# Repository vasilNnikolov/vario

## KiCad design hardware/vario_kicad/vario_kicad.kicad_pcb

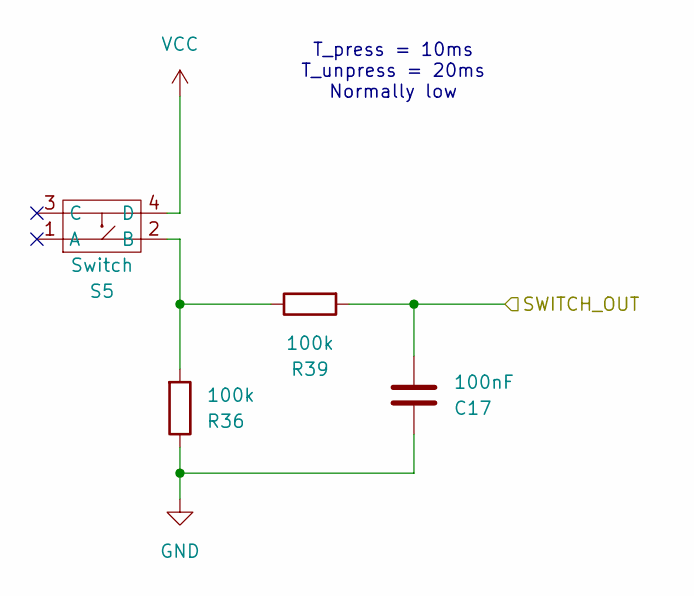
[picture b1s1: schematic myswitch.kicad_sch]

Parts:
C17: 100nF; C_0402_1005Metric
R36, R39: 100k; R_0402_1005Metric
S5: Switch; TS-1187A-B-A-B_switch

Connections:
/mcu/WKUP1: C17.2, R39.2; also elsewhere on the board
GND: C17.1, R36.1; also elsewhere on the board
unnamed: R36.2, R39.1, S5.2 (B)
VCC: S5.4 (D); also elsewhere on the board

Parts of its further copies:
C16, C28: 100nF; C_0402_1005Metric
R27, R37, R38, R40: 100k; R_0402_1005Metric
S4, S6: Switch; TS-1187A-B-A-B_switch

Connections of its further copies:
/mcu/SW1: C16.2, R38.2; also elsewhere on the board
/mcu/SW3: C28.2, R40.2; also elsewhere on the board
GND: C16.1, C28.1, R27.1, R37.1; also elsewhere on the board
unnamed: R27.2, R38.1, S4.2 (B)
unnamed: R37.2, R40.1, S6.2 (B)
VCC: S4.4 (D), S6.4 (D); also elsewhere on the board

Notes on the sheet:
T_press = 10ms T_unpress = 20ms Normally low

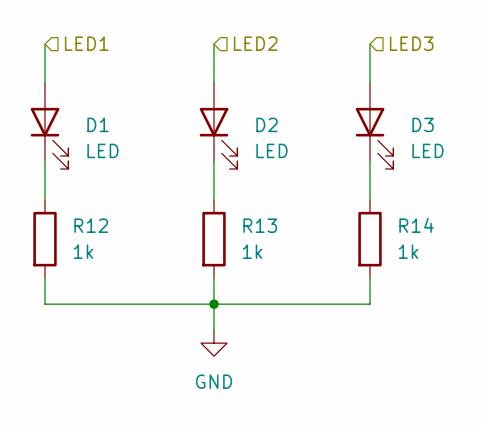
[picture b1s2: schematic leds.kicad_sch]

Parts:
D1, D2, D3: LED; LED_0603_1608Metric_Pad1.05x0.95mm_HandSolder
R12, R13, R14: 1k; R_0402_1005Metric

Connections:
/leds/LED1: D1.2 (A); also elsewhere on the board
/leds/LED2: D2.2 (A); also elsewhere on the board
/leds/LED3: D3.2 (A); also elsewhere on the board
GND: R12.2, R13.2, R14.2; also elsewhere on the board
unnamed: D1.1 (K), R12.1
unnamed: D2.1 (K), R13.1
unnamed: D3.1 (K), R14.1

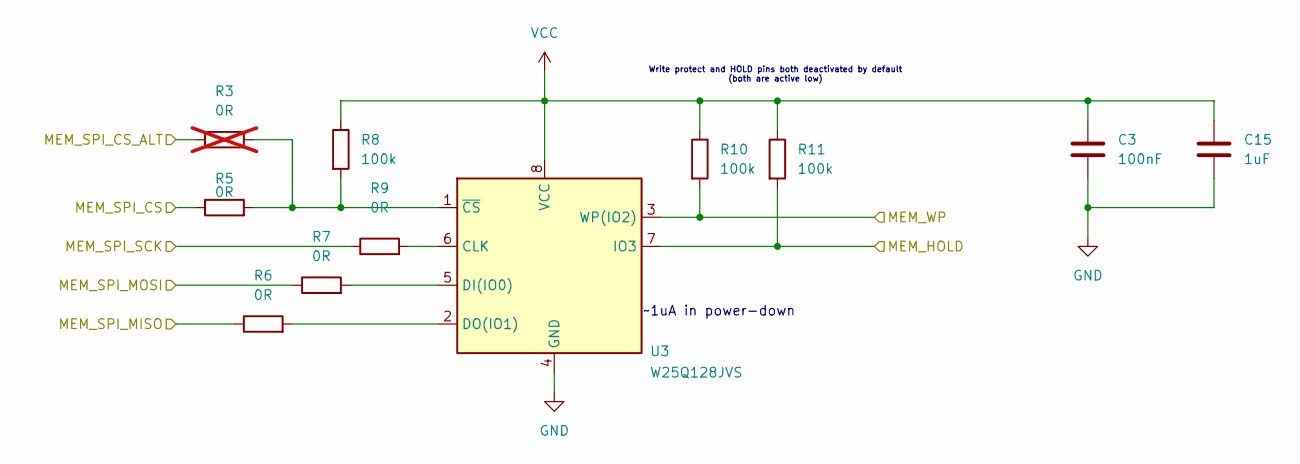
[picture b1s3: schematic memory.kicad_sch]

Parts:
C3: 100nF; C_0402_1005Metric
C15: 1uF; C_0402_1005Metric
R3: 0R; R_0402_1005Metric; not fitted
R5, R6, R7, R9: 0R; R_0402_1005Metric
R8, R10, R11: 100k; R_0402_1005Metric
U3: W25Q128JVS; SOIC-8_5.23x5.23mm_P1.27mm

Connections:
/mcu/MEM_CS_ALT: R3.1; also elsewhere on the board
/mcu/MEM_HOLD: R11.2, U3.7 (IO3); also elsewhere on the board
/mcu/MEM_WP: R10.2, U3.3 (WP(IO2)); also elsewhere on the board
/mcu/SPI1_MISO: R6.1; also elsewhere on the board
/mcu/SPI1_MOSI: R7.1; also elsewhere on the board
/mcu/SPI1_NSS: R5.1; also elsewhere on the board
/mcu/SPI1_SCK: R9.1; also elsewhere on the board
GND: C3.2, C15.2, U3.4 (GND); also elsewhere on the board
unnamed: R9.2, U3.6 (CLK)
unnamed: R7.2, U3.5 (DI(IO0))
unnamed: R6.2, U3.2 (DO(IO1))
unnamed: R3.2, R5.2, R8.2, U3.1 (~CS)
VCC: C3.1, C15.1, R8.1, R10.1, R11.1, U3.8 (VCC); also elsewhere on the board

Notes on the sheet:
Write protect and HOLD pins both deactivated by default (both are active low)
~1uA in power-down

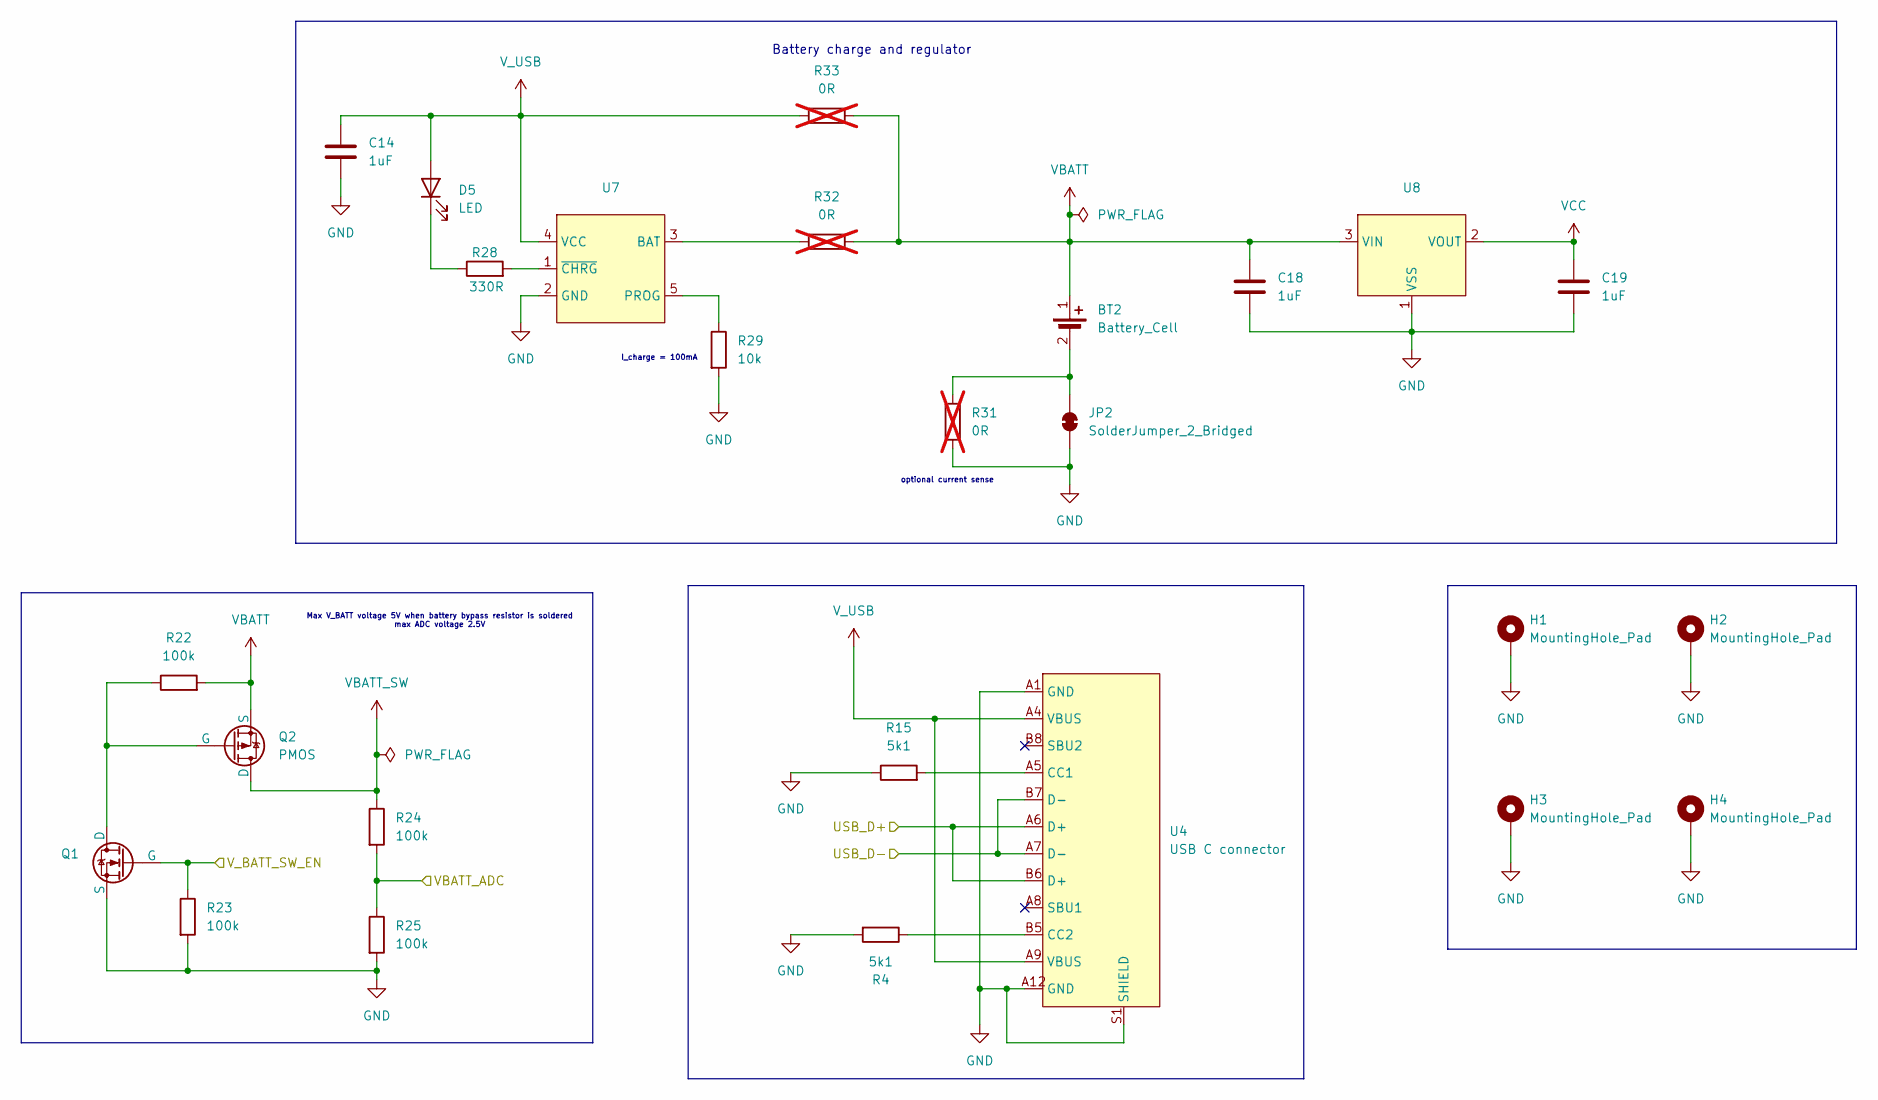
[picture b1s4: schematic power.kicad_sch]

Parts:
BT2: Battery_Cell; battery_th
C14, C18, C19: 1uF; C_0402_1005Metric
D5: LED; LED_0603_1608Metric_Pad1.05x0.95mm_HandSolder
H1, H2, H3, H4: MountingHole_Pad; MountingHole_2.2mm_M2_ISO7380_Pad
JP2: SolderJumper_2_Bridged; SolderJumper-2_P1.3mm_Open_TrianglePad1.0x1.5mm
Q1: NMOS; SOT-23_Handsoldering
Q2: PMOS; SOT-23_Handsoldering
R4, R15: 5k1; R_0402_1005Metric
R22, R23, R24, R25: 100k; R_0402_1005Metric
R28: 330R; R_0402_1005Metric
R29: 10k; R_0402_1005Metric
R31, R32, R33: 0R; R_0402_1005Metric; not fitted
U4: USB C connector; my_usbc
U7: SOT-23-5
U8: SOT-23

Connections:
/mcu/ADC_IN3: R24.2, R25.1; also elsewhere on the board
/mcu/USB_D+: U4.A6 (D+), U4.B6 (D+); also elsewhere on the board
/mcu/USB_D-: U4.A7 (D-), U4.B7 (D-); also elsewhere on the board
/mcu/VBATT_SW_EN: Q1.1 (G), R23.1; also elsewhere on the board
GND: C14.2, C18.2, C19.2, H1.1, H2.1, H3.1, H4.1, JP2.1 (A), Q1.2 (S), R4.2, R15.1, R23.2, R25.2, R29.2, R31.2, U4.A1 (GND), U4.A12 (GND), U4.S1 (SHIELD), U7.2 (GND), U8.1 (VSS); also elsewhere on the board
unnamed: BT2.2 (-), JP2.2 (B), R31.1
unnamed: D5.1 (K), R28.1
unnamed: Q1.3 (D), Q2.1 (G), R22.1
unnamed: R15.2, U4.A5 (CC1)
unnamed: R4.1, U4.B5 (CC2)
unnamed: R32.1, U7.3 (BAT)
unnamed: R29.1, U7.5 (PROG)
unnamed: R28.2, U7.1 (~CHRG)
VBATT: BT2.1 (+), C18.1, Q2.2 (S), R22.2, R32.2, R33.2, U8.3 (VIN)
VBATT_SW: Q2.3 (D), R24.1; also elsewhere on the board
VCC: C19.1, U8.2 (VOUT); also elsewhere on the board
V_USB: C14.1, D5.2 (A), R33.1, U4.A4 (VBUS), U4.A9 (VBUS), U7.4 (VCC)

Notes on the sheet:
I_charge = 100mA
optional current sense
Max V_BATT voltage 5V when battery bypass resistor is soldered max ADC voltage 2.5V
Battery charge and regulator

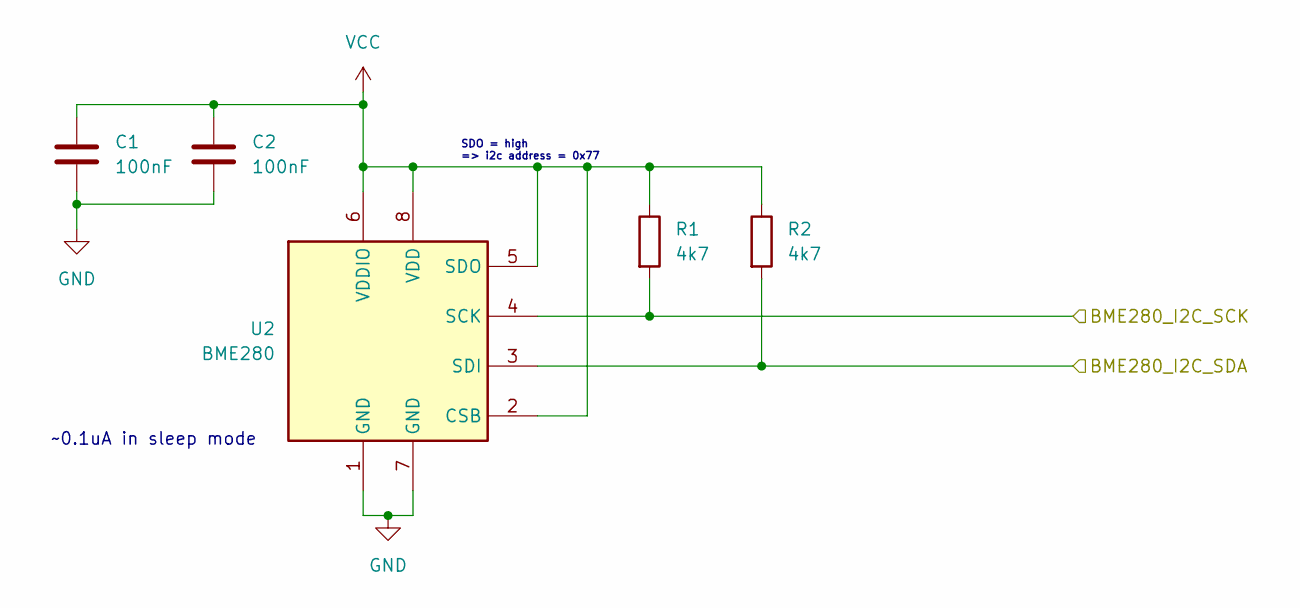
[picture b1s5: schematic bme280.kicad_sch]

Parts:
C1, C2: 100nF; C_0402_1005Metric
R1, R2: 4k7; R_0402_1005Metric
U2: BME280; Bosch_LGA-8_2.5x2.5mm_P0.65mm_ClockwisePinNumbering

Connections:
/bme280/BME280_I2C_SCK: R1.2, U2.4 (SCK); also elsewhere on the board
/bme280/BME280_I2C_SDA: R2.2, U2.3 (SDI); also elsewhere on the board
GND: C1.2, C2.2, U2.1 (GND), U2.7 (GND); also elsewhere on the board
VCC: C1.1, C2.1, R1.1, R2.1, U2.2 (CSB), U2.5 (SDO), U2.6 (VDDIO), U2.8 (VDD); also elsewhere on the board

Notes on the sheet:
SDO = high => i2c address = 0x77
~0.1uA in sleep mode

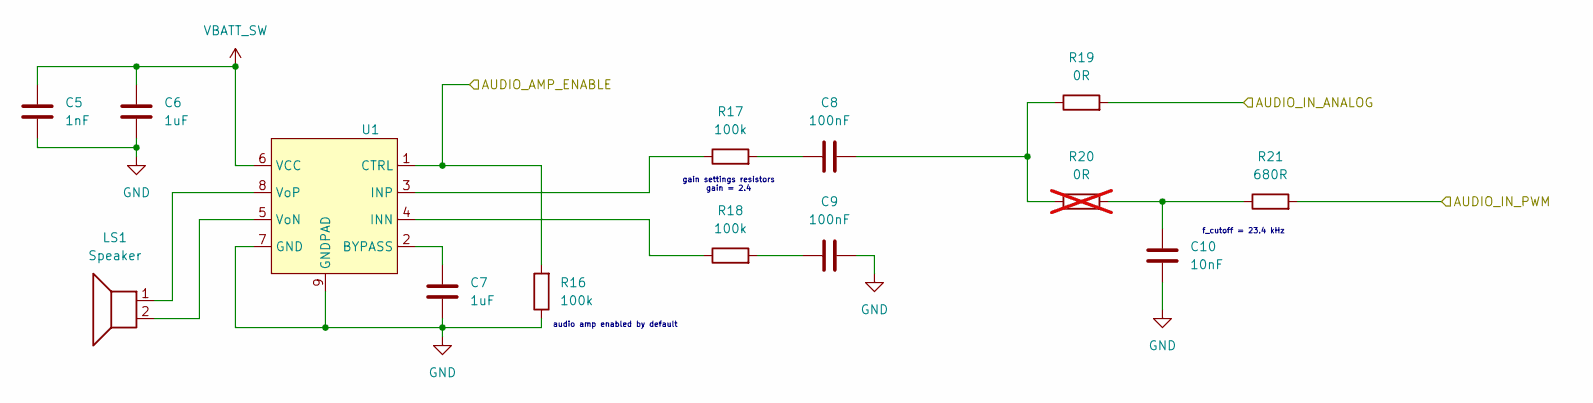
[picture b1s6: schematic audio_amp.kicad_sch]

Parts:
C5: 1nF; C_0402_1005Metric
C6, C7: 1uF; C_0402_1005Metric
C8, C9: 100nF; C_0402_1005Metric
C10: 10nF; C_0402_1005Metric
LS1: Speaker; speaker_footprint
R16, R17, R18: 100k; R_0402_1005Metric
R19: 0R; R_0402_1005Metric
R20: 0R; R_0402_1005Metric; not fitted
R21: 680R; R_0402_1005Metric
U1: MSOP-8-1EP_3x3mm_P0.65mm_EP2.5x3mm_Mask1.73x2.36mm

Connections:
/audio_amp/AUDIO_AMP_ENABLE: R16.2, U1.1 (CTRL); also elsewhere on the board
/audio_amp/AUDIO_IN_ANALOG: R19.2; also elsewhere on the board
/audio_amp/AUDIO_IN_PWM: R21.2; also elsewhere on the board
GND: C5.2, C6.2, C7.2, C9.2, C10.2, R16.1, U1.7 (GND), U1.9 (GNDPAD); also elsewhere on the board
unnamed: C8.1, R17.2
unnamed: C8.2, R19.1, R20.1
unnamed: C9.1, R18.2
unnamed: C10.1, R20.2, R21.1
unnamed: C7.1, U1.2 (BYPASS)
unnamed: R18.1, U1.4 (INN)
unnamed: R17.1, U1.3 (INP)
unnamed: LS1.2, U1.5 (VoN)
unnamed: LS1.1, U1.8 (VoP)
VBATT_SW: C5.1, C6.1, U1.6 (VCC); also elsewhere on the board

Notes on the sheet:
audio amp enabled by default
f_cutoff = 23.4 kHz
gain settings resistors gain = 2.4

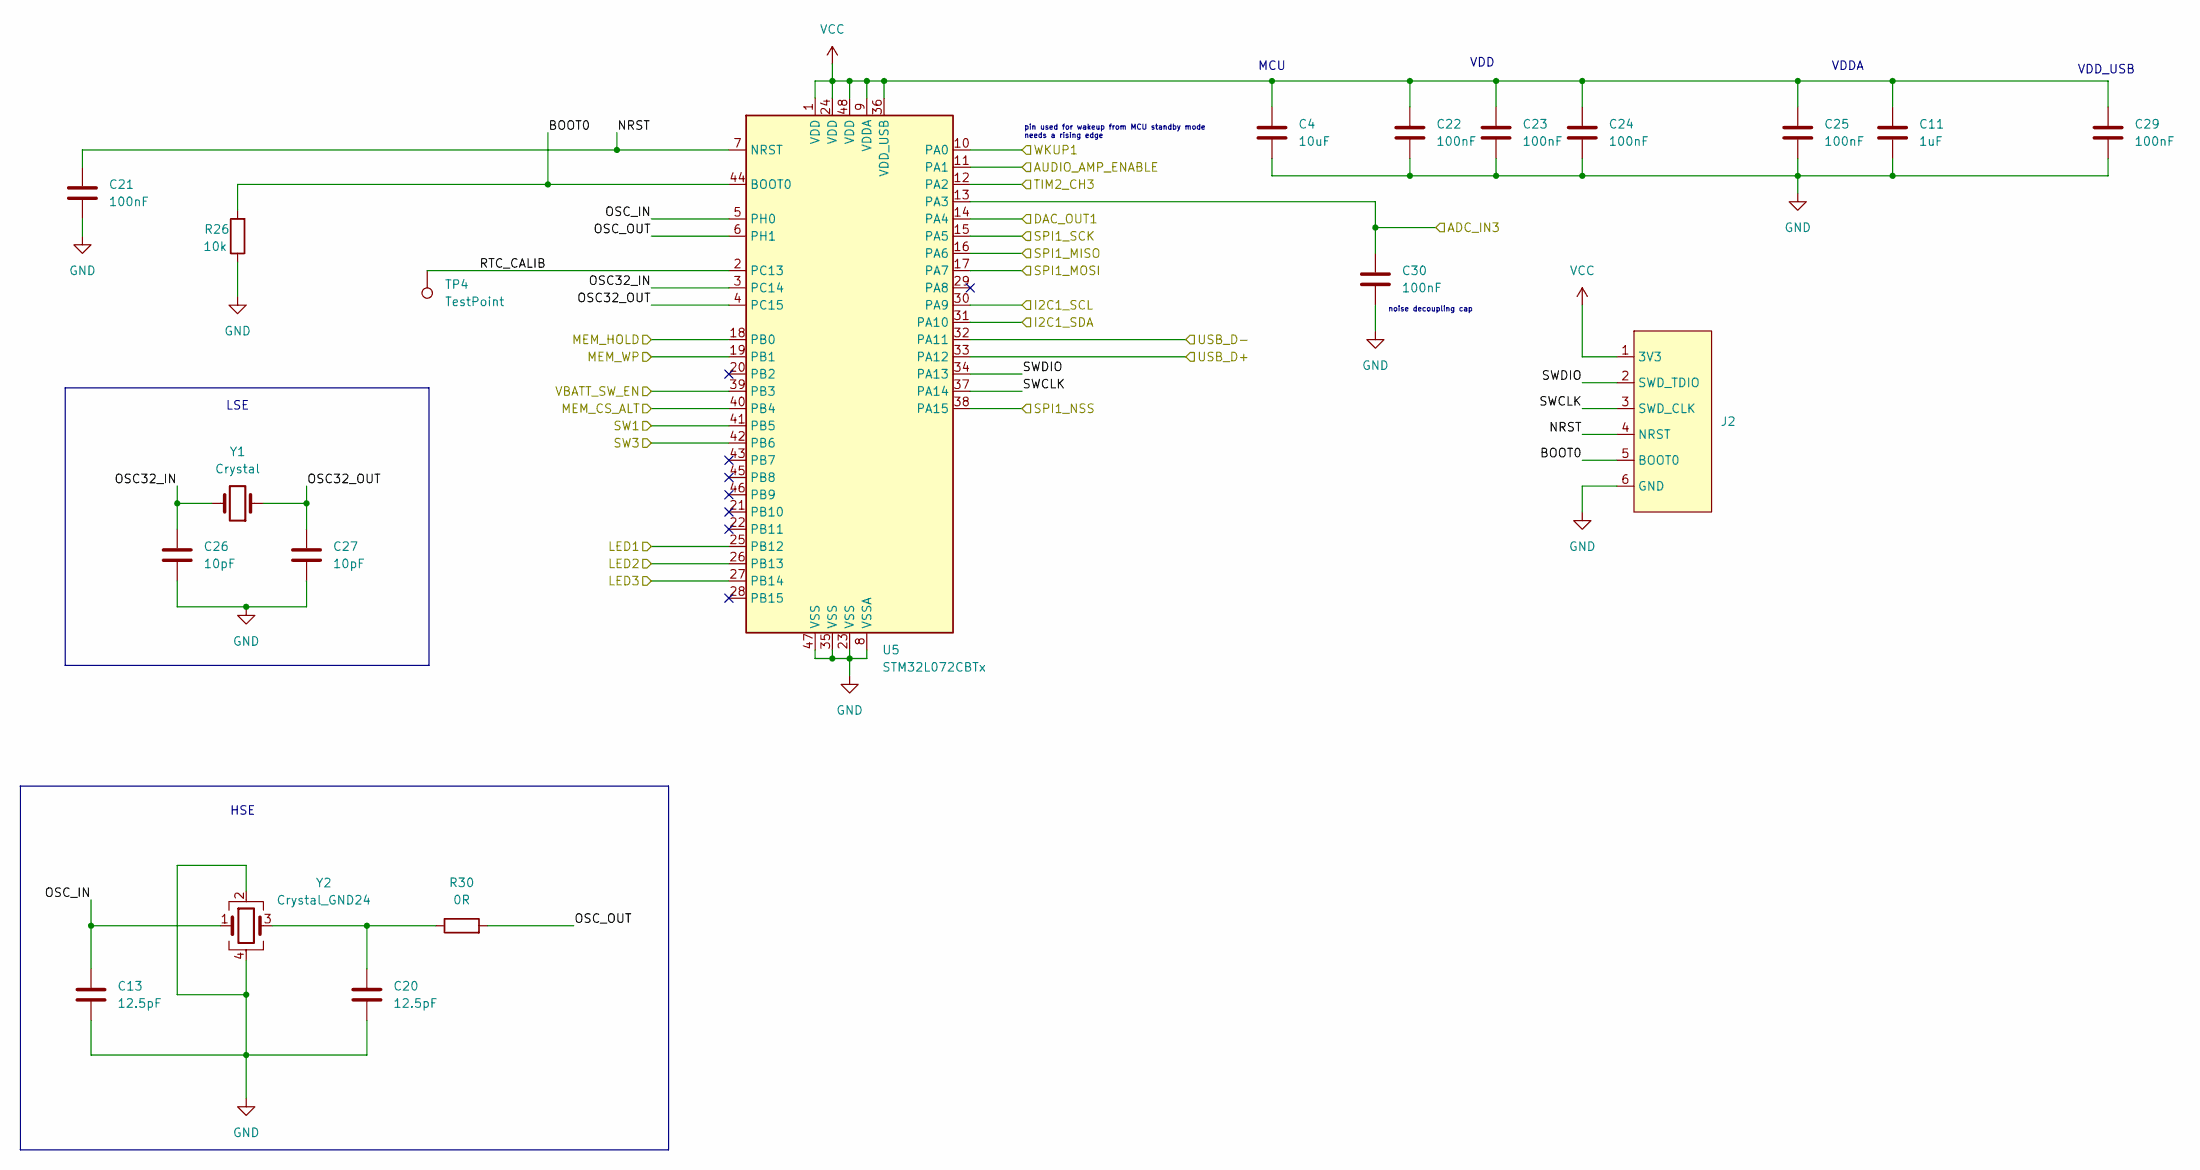
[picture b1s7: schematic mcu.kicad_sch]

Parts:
C4: 10uF; C_0603_1608Metric_Pad1.08x0.95mm_HandSolder
C11: 1uF; C_0402_1005Metric
C13, C20: 12.5pF; C_0402_1005Metric
C21, C22, C23, C24, C25, C29, C30: 100nF; C_0402_1005Metric
C26, C27: 10pF; C_0402_1005Metric
J2: SWD_programming
R26: 10k; R_0402_1005Metric
R30: 0R; R_0402_1005Metric
TP4: TestPoint; TestPoint_Pad_D1.0mm
U5: STM32L072CBTx; LQFP-48_7x7mm_P0.5mm
Y1: Crystal; Crystal_SMD_2012-2Pin_2.0x1.2mm_HandSoldering
Y2: Crystal_GND24; Crystal_SMD_3225-4Pin_3.2x2.5mm

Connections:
/audio_amp/AUDIO_AMP_ENABLE: U5.11 (PA1); also elsewhere on the board
/audio_amp/AUDIO_IN_ANALOG: U5.14 (PA4); also elsewhere on the board
/audio_amp/AUDIO_IN_PWM: U5.12 (PA2); also elsewhere on the board
/bme280/BME280_I2C_SCK: U5.30 (PA9); also elsewhere on the board
/bme280/BME280_I2C_SDA: U5.31 (PA10); also elsewhere on the board
/leds/LED1: U5.25 (PB12); also elsewhere on the board
/leds/LED2: U5.26 (PB13); also elsewhere on the board
/leds/LED3: U5.27 (PB14); also elsewhere on the board
/mcu/ADC_IN3: C30.1, U5.13 (PA3); also elsewhere on the board
/mcu/BOOT0: J2.5 (BOOT0), R26.2, U5.44 (BOOT0)
/mcu/MEM_CS_ALT: U5.40 (PB4); also elsewhere on the board
/mcu/MEM_HOLD: U5.18 (PB0); also elsewhere on the board
/mcu/MEM_WP: U5.19 (PB1); also elsewhere on the board
/mcu/NRST: C21.1, J2.4 (NRST), U5.7 (NRST)
/mcu/OSC32_IN: C26.1, U5.3 (PC14), Y1.2
/mcu/OSC32_OUT: C27.1, U5.4 (PC15), Y1.1
/mcu/OSC_IN: C13.1, U5.5 (PH0), Y2.1
/mcu/OSC_OUT: R30.2, U5.6 (PH1)
/mcu/RTC_CALIB: TP4.1, U5.2 (PC13)
/mcu/SPI1_MISO: U5.16 (PA6); also elsewhere on the board
/mcu/SPI1_MOSI: U5.17 (PA7); also elsewhere on the board
/mcu/SPI1_NSS: U5.38 (PA15); also elsewhere on the board
/mcu/SPI1_SCK: U5.15 (PA5); also elsewhere on the board
/mcu/SW1: U5.41 (PB5); also elsewhere on the board
/mcu/SW3: U5.42 (PB6); also elsewhere on the board
/mcu/SWCLK: J2.3 (SWD_CLK), U5.37 (PA14)
/mcu/SWDIO: J2.2 (SWD_TDIO), U5.34 (PA13)
/mcu/USB_D+: U5.33 (PA12); also elsewhere on the board
/mcu/USB_D-: U5.32 (PA11); also elsewhere on the board
/mcu/VBATT_SW_EN: U5.39 (PB3); also elsewhere on the board
/mcu/WKUP1: U5.10 (PA0); also elsewhere on the board
GND: C4.2, C11.2, C13.2, C20.2, C21.2, C22.2, C23.2, C24.2, C25.2, C26.2, C27.2, C29.2, C30.2, J2.6 (GND), R26.1, U5.8 (VSSA), U5.23 (VSS), U5.35 (VSS), U5.47 (VSS), Y2.2, Y2.4; also elsewhere on the board
unnamed: C20.1, R30.1, Y2.3
VCC: C4.1, C11.1, C22.1, C23.1, C24.1, C25.1, C29.1, J2.1 (3V3), U5.1 (VDD), U5.9 (VDDA), U5.24 (VDD), U5.36 (VDD_USB), U5.48 (VDD); also elsewhere on the board

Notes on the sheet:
pin used for wakeup from MCU standby mode needs a rising edge
VDD_USB
LSE
VDD
noise decoupling cap
MCU
HSE
VDDA

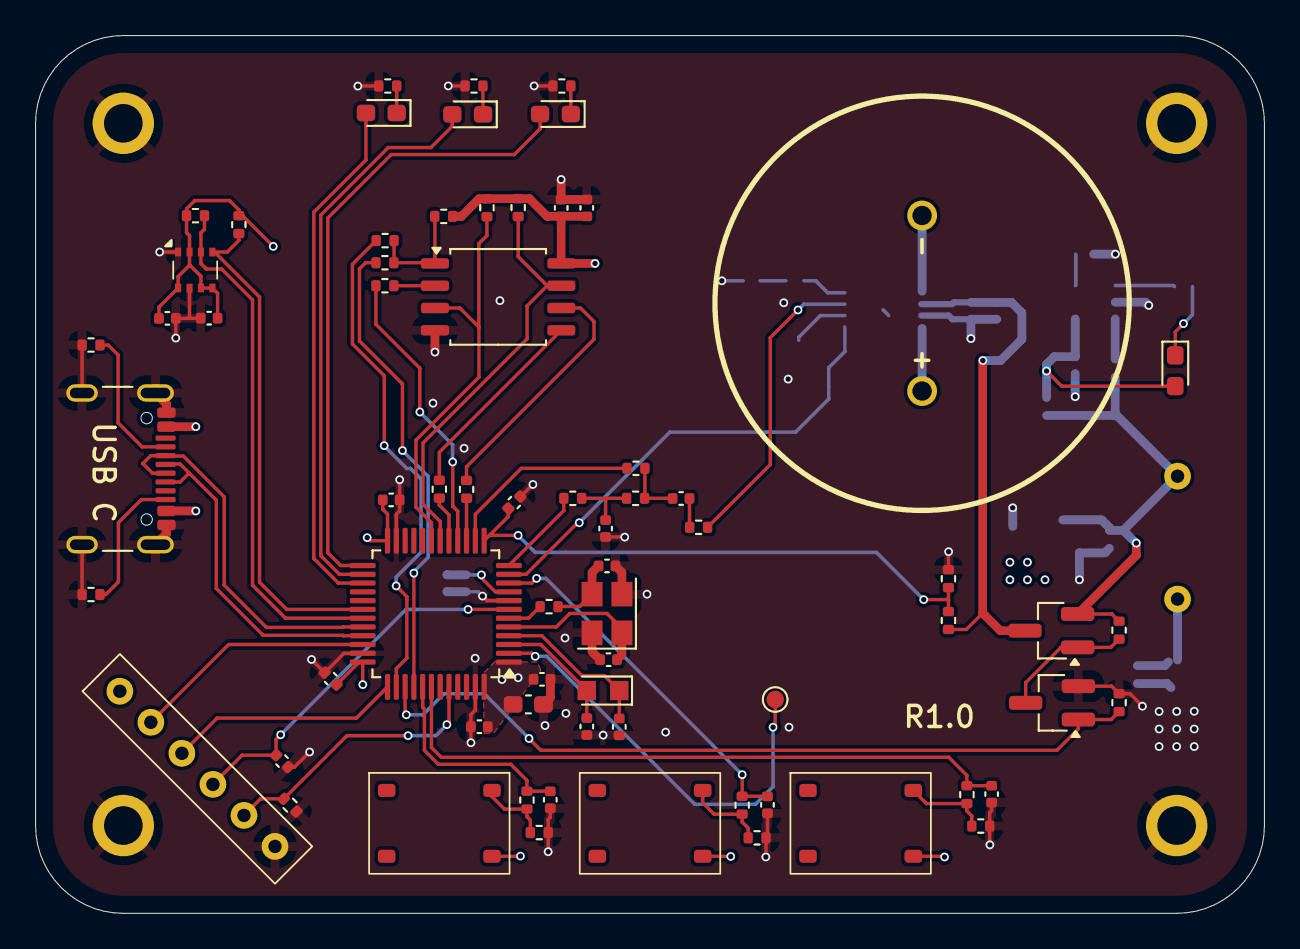
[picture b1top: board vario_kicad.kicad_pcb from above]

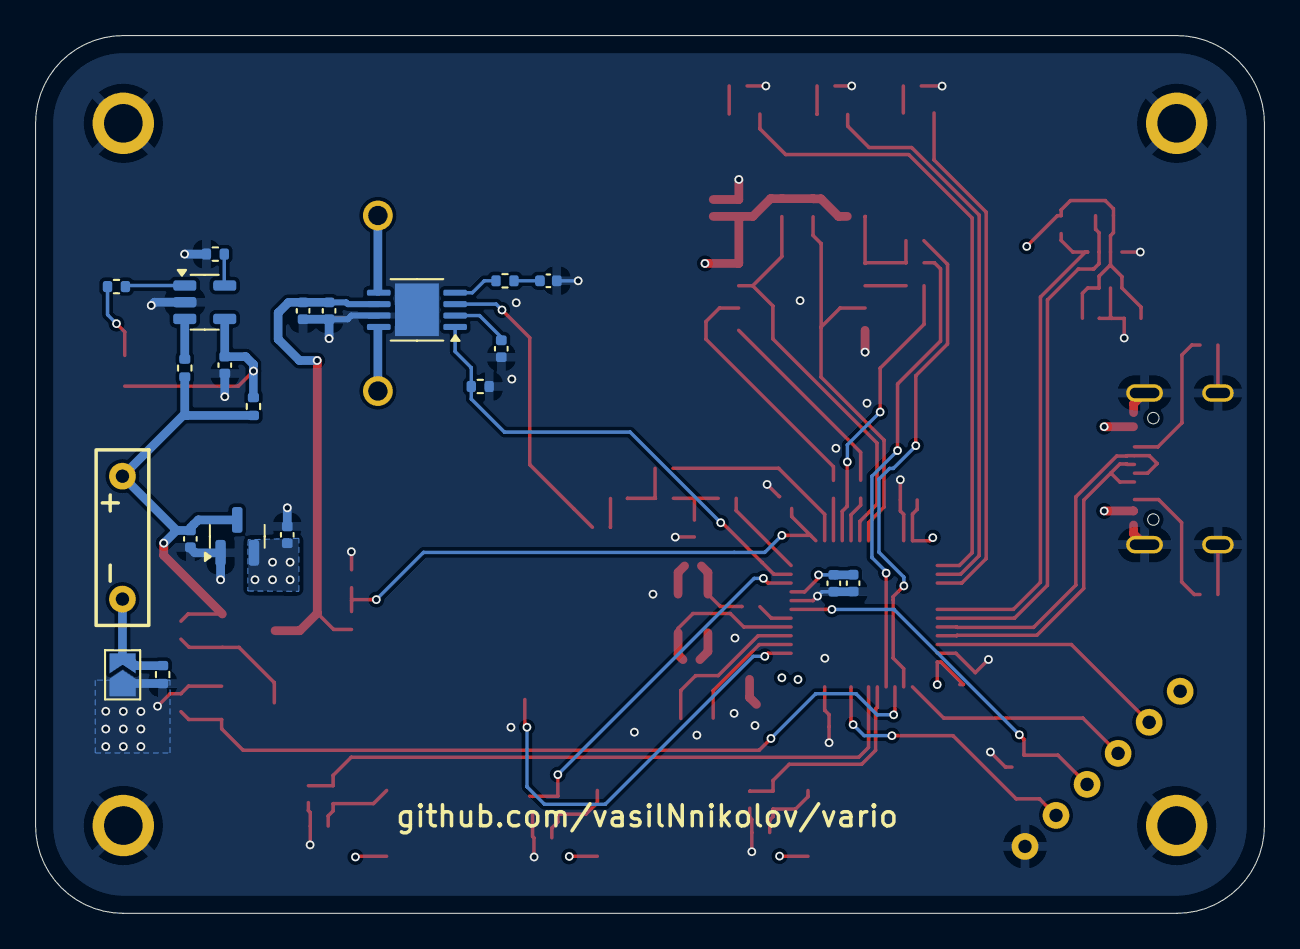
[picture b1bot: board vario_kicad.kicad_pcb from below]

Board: 4 copper layers, 70.0 x 50.0 mm, 94 parts (21 on the bottom side), 64 nets.

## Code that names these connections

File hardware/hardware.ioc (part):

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Mcu.Name=STM32L072C(B-Z)Tx
Mcu.Package=LQFP48
Mcu.UserName=STM32L072CBTx
PA10.Mode=I2C
PA10.Signal=I2C1_SDA
PA11.Mode=Device
PA11.Signal=USB_DM
PA12.Mode=Device
PA12.Signal=USB_DP
PA13.Mode=Serial_Wire
PA13.Signal=SYS_SWDIO
PA14.Mode=Serial_Wire
PA14.Signal=SYS_SWCLK
PA15.Mode=NSS_Signal_Hard_Output
PA15.Signal=SPI1_NSS
PA3.Mode=IN3
PA3.Signal=ADC_IN3
PA4.Signal=COMP_DAC1_group
PA5.Mode=Full_Duplex_Master
PA5.Signal=SPI1_SCK
PA6.Mode=Full_Duplex_Master
PA6.Signal=SPI1_MISO
PA7.Mode=Full_Duplex_Master
PA7.Signal=SPI1_MOSI
PA9.Mode=I2C
PA9.Signal=I2C1_SCL
PB3.Signal=GPIO_Output
RCC.HSE_VALUE=8000000
RCC.SYSCLKFreq_VALUE=2097000
board=custom

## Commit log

2024-05-01 add readme and gitignore
2024-05-01 blinky compiles and runs
2024-05-04 add bme280 library
2024-05-08 figured out defmt
2024-05-08 BME works!!
2024-05-11 use bme280 as a local dependency
2024-05-13 add h, v computation
2024-05-14 use normal mode is successful
2024-05-20 add config for sensor
2024-05-20 better integration
2024-05-22 try to add fir
2024-05-23 moving average fir
2024-05-28 add csv logger
2024-05-29 random stuff unfinished
2024-06-04 add basic pwm logic
2024-07-01 beeper WIP
2024-07-05 beeping worksV
2025-01-19 sync
2025-02-18 begin project for stm32 board
2025-02-21 add project from embedded rust book, adapt to STM32L071CB
2025-02-21 add stm32l071 pac
2025-02-21 add defmt as dependency
2025-02-21 add blinky
2025-02-21 update schematic
2025-02-22 continue with stm32 only
2025-02-22 add documentation in mkdocs
2025-02-22 add external memory chip
2025-02-25 update hw
2025-02-28 update to stm32l072 processor for usb
2025-03-01 afsd
2025-03-02 add NS4150B symbol
2025-03-05 update schematic, add stm32mx file
2025-03-07 add power supply
2025-03-11 updates;
2025-03-13 add push button switches
2025-03-16 minor updates
2025-03-17 update some component footprints
2025-03-18 move external components to separate sheets
2025-03-20 all components in hier sheets
2025-03-22 add hw design guide
2025-03-26 update footprints, add LSE oscillator
2025-03-28 start layout
2025-03-29 minor change
2025-03-30 update usb c, minor other updates
2025-04-01 add persistent counters in flash, untested
2025-04-01 add critical_section dependency
2025-04-02 start v1 schematic review
2025-04-02 v1 review of mcu
2025-04-02 v1 review of power
2025-04-04 add HSE to the MCU
2025-04-04 add test point to audio input
2025-04-04 add footprints
2025-04-04 better switch debounce
2025-04-04 update switch de-bouncing
2025-04-04 minor update to memory, untested
2025-04-07 fix memory schematic, update button switches
    - fix miso/mosi mistake: miso->miso, mosi->mosi
    - WKUP1 needs a rising edge to wake up the MCU, so all switch logic was
    reversed
2025-04-08 add RTC_CALIB test point
2025-04-08 add optional resistor for HSE oscillator
2025-04-08 minor changes
2025-04-08 add optional current sense resistor
2025-04-08 add 2 missing GND pins to MCU symbol
2025-04-08 move LED1 as FTf vs FT does not matter
2025-04-08 fix erc
2025-04-09 add solder bridge to disconnect battery from charger
2025-04-09 do not connect MCU to VBATT
2025-04-10 use correct pac
2025-04-10 add courtyard to switch and speaker
2025-04-10 smaller max value for BP voltage divider
2025-04-10 add power symbol for ERC
2025-04-10 add decoupling capacitor for vdd_usb
2025-04-10 add missing footprints
2025-04-11 remove useless test points
2025-04-11 remove more testpoints
2025-04-11 use all 4 USB D+/- pins
2025-04-11 progress update on layout
2025-04-11 layout close to done
2025-04-11 asdf
2025-04-12 remove unnecessary jumper
2025-04-12 use 0402 instead of 0603 for almost all caps
2025-04-12 begin routing
2025-04-12 routing progress
2025-04-12 layout close to finished
2025-04-13 layout&routing close to done
2025-04-15 update usb c footprint for drc
    shrink the usb c footprint pads closest to the NPTH mounting holes to
    satisfy the DRC min distance 0.2mm hole to copper
2025-04-21 remove jumper connecting charger to battery
2025-04-21 updates to layout v2
2025-04-23 update layout v2
2025-04-24 remove capacitor to boot0 pin
2025-04-24 almost finish 4layer board
2025-04-24 minor fixes
2025-04-25 finalize v2 layout
2025-04-26 make switches symmetrical
2025-04-28 minor updates to power schematic
    - add optional battery bypass resistor between USB power and 3.3V regulator
    - make VBATT voltage divider use the more common 100k resistor
2025-04-28 design almost finished
2025-04-29 minor changes to layout
2025-04-29 move LSE to bottom of board, move HSE closer to MCU
2025-04-30 modify silkscreen
2025-05-04 finished board variant 1, LSE on bottom
2025-05-04 finished layout variant 2
    - LSE on top
    - increased clearance of copper pours
2025-05-04 remove some examples from the cortex-m-quickstart repo
2025-05-05 restructure the software
2025-05-05 derive default on bindings
2025-05-05 remove workspace
2025-05-05 vario bin compiles successfully
2025-05-05 bindings for the right architecture
2025-05-05 improve c bindings
2025-05-06 better compilation
2025-05-07 add busy loop blinky
2025-05-08 add systick example
2025-05-08 add pdf schematic
2025-05-08 add code for tim6, RCC_CIER register is wrong in SVD files
2025-05-26 add cpac crate
2025-05-27 minor improvements
2025-05-29 use workspace
2025-05-29 clear warning for unsafe_op_in_unsafe_fn from bindgen
2025-06-02 running from app works, from sw does not work
2025-06-03 do not use workspace as it's not needed atm
2025-06-03 separate HW and SW docs
2025-06-03 add .gitignore for SW crates
2025-06-03 minor refactoring
2025-06-03 remove not-finished reset counters
2025-06-03 add docs for flashing
2025-06-03 minor fixes, blinky does not work
2025-06-04 triply blinky works
2025-06-05 c bindings in OUT_DIR
2025-06-05 defmt buggs out from asm::wfi
2025-06-05 add proc-macro to create a nice PAC
2025-06-06 basic proc macro works
2025-06-06 add module
2025-06-06 better macro
2025-06-06 add constants programatically
2025-06-07 add BASE constant parsing
2025-06-07 add RW, not working due to imports
2025-06-09 volatile_register works, TODO fix
    - volatile_register dependency is in PAC, should be provided by macro
    - both single registers (u32) and arrays of registers (ex. [u32; 5]) are
    wrapped in RW<T>, arrays should turn into [RW<u32>; 5]
2025-06-10 minor update, looks ready for work
2025-06-10 add cpac, not yet finished
2025-06-11 remove prefix from constants
    Ex. if in the bindings a constant was RCC_AHBENR,
    it will be just rcc::AHBENR in the rcc module
2025-06-13 code compiles but does not work
2025-06-14 should work
2025-06-15 blinky_cpac should work, untested
2025-06-16 blinky_cpac works
2025-06-16 add simpler modify_field function, ZCA to modify_register
2025-06-16 switched to HSE, somehow it's slower than expected
2025-06-18 add systick uptime counter
2025-06-19 logging works in sleep mode
2025-06-20 add rtc peripheral to cpac
2025-06-24 rtc works
2025-06-25 always initialize the RTC to the current time
2025-06-25 add RTC calib output to PC13
2025-07-03 read state of SW1
2025-07-05 parse [T; N] into [RW<T>; N]
2025-07-05 add sw1 reading with interrupts
2025-07-07 move init functions to bsp
2025-07-14 no queue, small refactor
2025-07-15 add dependencies, no work done
2025-07-17 barely any progress
2025-07-20 usb maybe works
2025-07-21 sw2 works
2025-07-21 standby mode does not work
2025-07-22 add blinking on startup
    - WKUP1 pulldown is messing up the switch debouncing logic
    - WKUP1 pulldown is present even after reset
    - device resets when it should enter standby mode
2025-07-23 standby works, suboptimal - has unnecessary clears (WUPF & CSBF) - after LED2 turns off, you need to immediately unpress SW2 to enter standby
2025-07-26 fix debounce circuit for wkup1
2025-07-26 add power-down LED sequence
2025-07-26 standby mode works without debugger
    with debugger, it executes the normal power-down sequence, however, the moment SW2 is pressed, the debugger exits with
    ```
    Firmware exited unexpectedly: Exception
    Core 0
    Frame 0: __INTERRUPTS @ 0x080000c0> @ 0x00000000080000c0
    Frame 1: Reset @ 0x00000000
2025-07-26 startup procedure works
2025-08-02 fix probe-rs blocking the app on standby exit
2025-09-16 add simple mpmc queue, WIP
2025-09-16 best practices
2025-09-19 progress
2025-09-19 add unfinished stress test
2025-09-22 todo pop should return the full element
2025-09-23 todo change storage from array to ptr
    an array of unsafecells needs each element to be aligned
